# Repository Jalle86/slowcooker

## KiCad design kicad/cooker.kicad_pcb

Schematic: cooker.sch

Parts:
R1, R2, R3: R
U1: ESP-01V090

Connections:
+3.3V: U1.3, U1.4, U1.5, U1.6, U1.7
unnamed: R1.2, R2.2
unnamed: R2.1, R3.1, U1.1

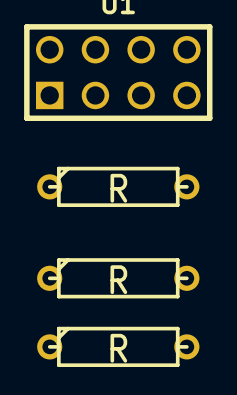
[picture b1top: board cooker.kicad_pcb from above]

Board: 2 copper layers, 4 parts (0 on the bottom side), 3 nets, no tracks yet.

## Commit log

2017-04-26 pulsgivare
2017-04-27 lcd klar pretty much
2017-04-28 sensor+lcd+pulsgivare
2017-05-02 ny vecka
2017-05-03 bluetooth
2017-05-04 wifi ellerrrrrr
2017-05-08 tolk påbörjad
2017-05-08 tolk + bt
2017-05-09 detaljer
2017-05-10 wifi och andra grejer
2017-05-11 some o that wifi
2017-05-15 omfaktoriserat koden
2017-05-17 tolk förbättrad
2017-05-18 autentiseringssystem + tolkförbättringar
2017-05-31 massa krejjer
2017-06-01 int så mkt...
2017-06-02 rapportolainen
2017-06-08 lotsa stuff
2017-06-09 rapportortorto
2017-06-13 final stretch
2017-06-14 wooop :o
2017-06-15 FLAWLESS VICTORY
